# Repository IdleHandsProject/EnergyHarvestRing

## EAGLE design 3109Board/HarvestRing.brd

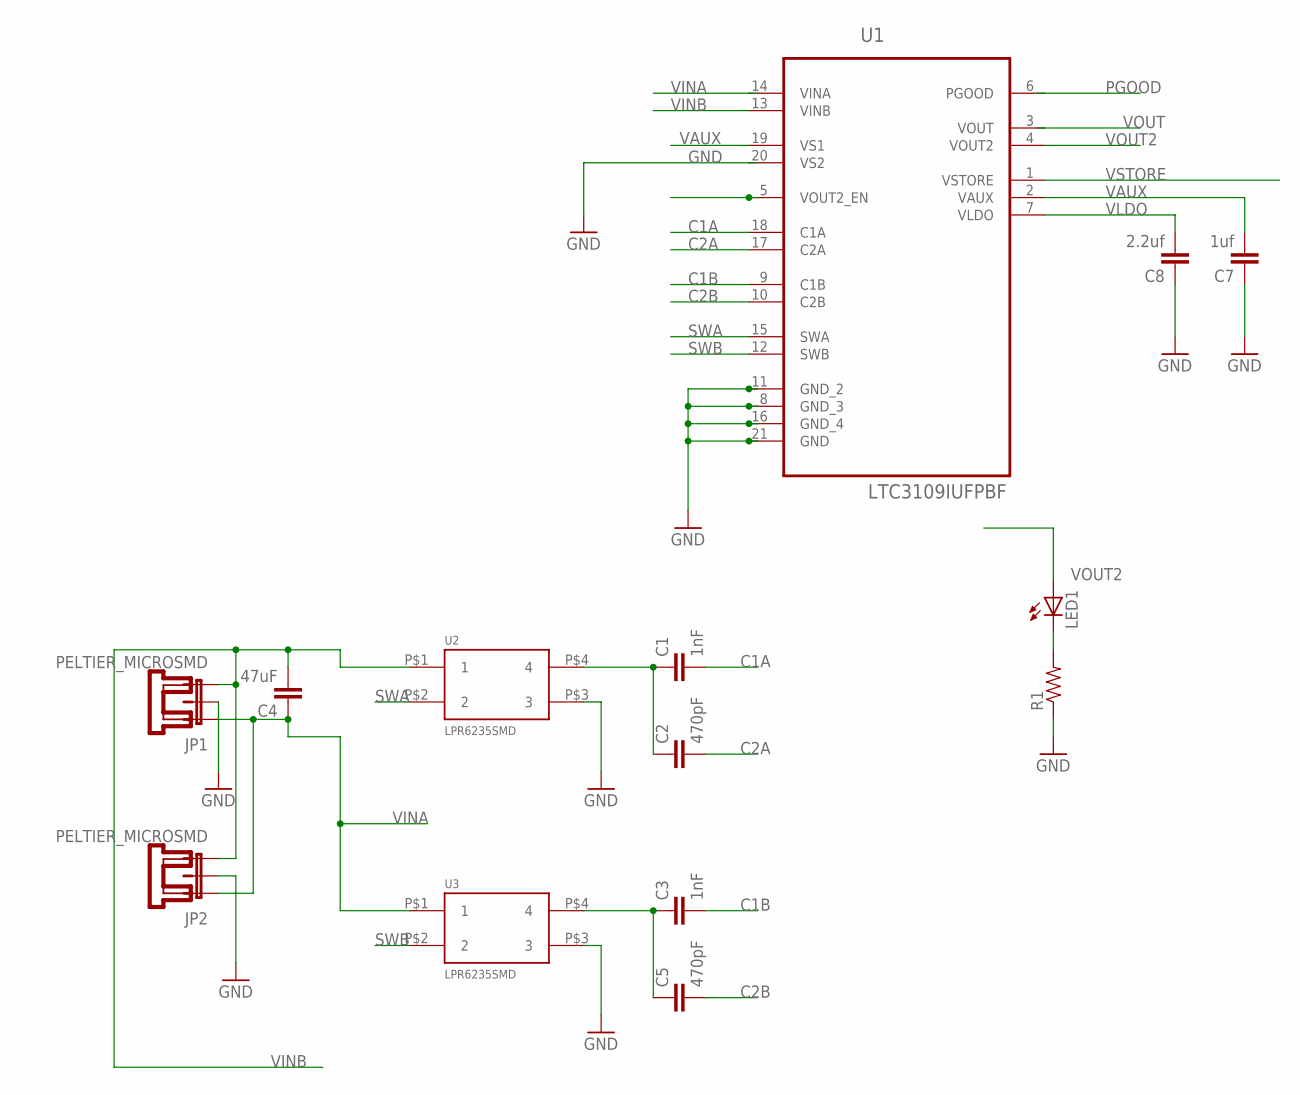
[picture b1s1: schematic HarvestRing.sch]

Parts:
C1, C3: 1nF; 0603-CAP
C2, C5: 470pF; 0603-CAP
C4: 47uF; 0603-CAP
C7: 1uf; 0603-CAP
C8: 2.2uf; 0603-CAP
JP1, JP2: PELTIER_MICROSMD; HV56
LED1: LED1206; LED-1206
R1: 22K; 0603-RES
U1: LTC3109IUFPBF; QFN50P400X400X80-21N
U2, U3: LPR6235SMD; LPR6235

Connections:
C1A: C1.2, U1.18 (C1A)
C1B: C3.2, U1.9 (C1B)
C2A: C2.2, U1.17 (C2A)
C2B: C5.2, U1.10 (C2B)
GND: C7.1, C8.1, JP1.2, JP2.2, R1.1, U1.8 (GND_3), U1.11 (GND_2), U1.16 (GND_4), U1.20 (VS2), U1.21 (GND), U2.P$3 (3), U3.P$3 (3)
unnamed: C1.1, C2.1, U2.P$4 (4)
unnamed: LED1.C, R1.2
unnamed: C3.1, C5.1, U3.P$4 (4)
PGOOD: U1.5 (VOUT2_EN), U1.6 (PGOOD)
SWA: U1.15 (SWA), U2.P$2 (2)
SWB: U1.12 (SWB), U3.P$2 (2)
VAUX: C7.2, U1.2 (VAUX), U1.19 (VS1)
VINA: C4.1, JP1.1, JP2.1, U1.14 (VINA), U3.P$1 (1)
VINB: C4.2, JP1.3, JP2.3, U1.13 (VINB), U2.P$1 (1)
VLDO: C8.2, U1.7 (VLDO)
VOUT: U1.3 (VOUT)
VOUT2: LED1.A, U1.4 (VOUT2)
VSTORE: U1.1 (VSTORE)

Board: 2 copper layers, 15 parts (0 on the bottom side), 16 nets, no tracks yet.

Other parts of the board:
U$1: ELIPSISLOGO-3MM

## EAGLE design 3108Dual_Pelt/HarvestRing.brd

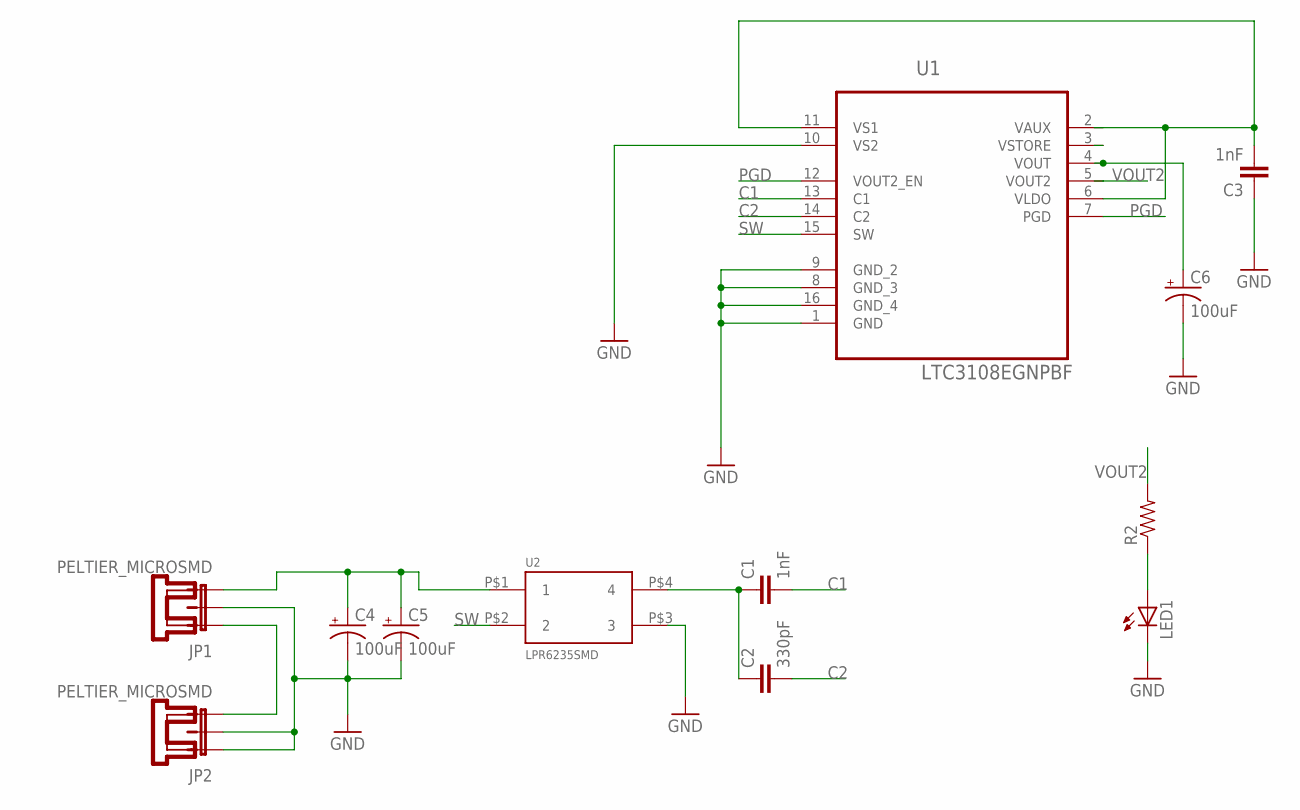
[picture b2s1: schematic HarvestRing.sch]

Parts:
C1, C3: 1nF; 0603-CAP
C2: 330pF; 0603-CAP
C4, C5, C6: 100uF; EIA3216
JP1, JP2: PELTIER_MICROSMD; HV56
LED1: LED1206; LED-1206
R2: 22K; 0603-RES
U1: LTC3108EGNPBF; SOP63P600X175-16N
U2: LPR6235SMD; LPR6235

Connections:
C1: C1.2, U1.13 (C1)
C2: C2.2, U1.14 (C2)
GND: C3.1, C4.C (-), C5.C (-), C6.C (-), JP1.2, JP2.1, JP2.2, LED1.C, U1.1 (GND), U1.8 (GND_3), U1.9 (GND_2), U1.10 (VS2), U1.16 (GND_4), U2.P$3 (3)
unnamed: C1.1, C2.1, U2.P$4 (4)
unnamed: C4.A (+), C5.A (+), JP1.3, U2.P$1 (1)
unnamed: JP1.1, JP2.3
unnamed: C3.2, U1.2 (VAUX), U1.6 (VLDO), U1.11 (VS1)
unnamed: C6.A (+), U1.4 (VOUT)
unnamed: LED1.A, R2.1
PGD: U1.7 (PGD), U1.12 (VOUT2_EN)
SW: U1.15 (SW), U2.P$2 (2)
VOUT2: R2.2, U1.5 (VOUT2)

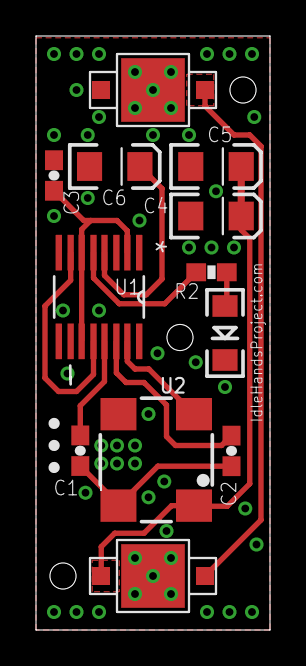
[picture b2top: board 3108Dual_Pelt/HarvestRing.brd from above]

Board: 2 copper layers, 13.0 x 33.0 mm, 13 parts (0 on the bottom side), 12 nets.

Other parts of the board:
U$1: ELIPSISLOGO-3MM

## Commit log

2014-02-11 Added Eagle Files
2014-02-12 Created and Modified ring PCB
    New ring pcb designed.
2014-05-26 Latest Ring Mod
    Check over before ordering

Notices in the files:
parts and their libraries:
SparkFun-Capacitors: Licensing: CC v3.0 Share-Alike You are welcome to use this library for commercial purposes.
